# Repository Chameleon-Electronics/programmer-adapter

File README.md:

<!--
Add one of this in front of the title

-->

# Programmer Adapter 

This board interfaces the SEGGER JLink to the boards of this collection

## SEGGER JLink
SEGGER J-Links are the most commonly used line of debug probes nowadays. Their growing popularity is the fruit of their high performance, the large number of CPUs they support, as well as development environments, and also their huge feature set. SEGGER J-Links have been available for more than 10 years, and in this period they've proven their resilience in the debug probes market.

## Features
### Functional

- Program and debug device
- Power the device through this board

### Technical

- None

<!--- DON'T CHANGE BELLOW THIS LINE -->

## Not working?
Please file an issue with all the details you can provide and we will fix it for you.

## Contributing
You are free to reach out and report issues, fix bugs and suggest new features as well as submit pull-requests.

## License
You can use this at your will provided that you mention us properly by including a link to this page. For further information, consult the [LICENSE](LICENSE) file.

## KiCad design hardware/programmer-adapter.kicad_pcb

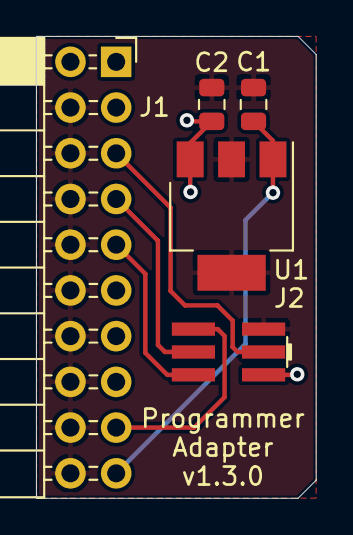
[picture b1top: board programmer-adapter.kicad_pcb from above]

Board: 2 copper layers, 15.5 x 25.7 mm, 5 parts (0 on the bottom side), 7 nets.

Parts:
C1: 10u; C_0805_2012Metric
C2: 22u; C_0805_2012Metric
J1: Conn_ARM_JTAG_SWD_20; PinSocket_2x10_P2.54mm_Horizontal
J2: Conn_Chameleon_SWD; Chameleon_SWD_Header
U1: MCP1826S; SOT-223-3_TabPin2

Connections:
+3V3: C2.1, J1.1, J2.1, U1.3
+5V: C1.1, J1.19, U1.1
/RX: J1.17, J2.6
/SWDCLK: J1.9, J2.2
/SWDIO: J1.7, J2.4
/TX: J1.5, J2.3
GND: C1.2, C2.2, J1.4, J1.6, J1.8, J1.10, J1.12, J1.14, J1.16, J1.18, J1.20, J2.5, U1.2

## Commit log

2020-02-21 fix libraries
2020-02-22 Added power designators
2020-02-22 Updated PCB 3D view
2020-03-10 Added reset signal
2020-03-10 Remove gerbers from repository
2020-06-01 Voltage Regulator Supply
2020-06-02 Changed LDO to MCP1826S
2020-07-05 VCOM connection
2020-07-05 Updated 3D Render
2020-07-05 Fill zones
2020-10-28 Pending Changes
2020-10-31 Add link to LICENSE file.
2020-10-31 Add info about SEGGER J-Links
